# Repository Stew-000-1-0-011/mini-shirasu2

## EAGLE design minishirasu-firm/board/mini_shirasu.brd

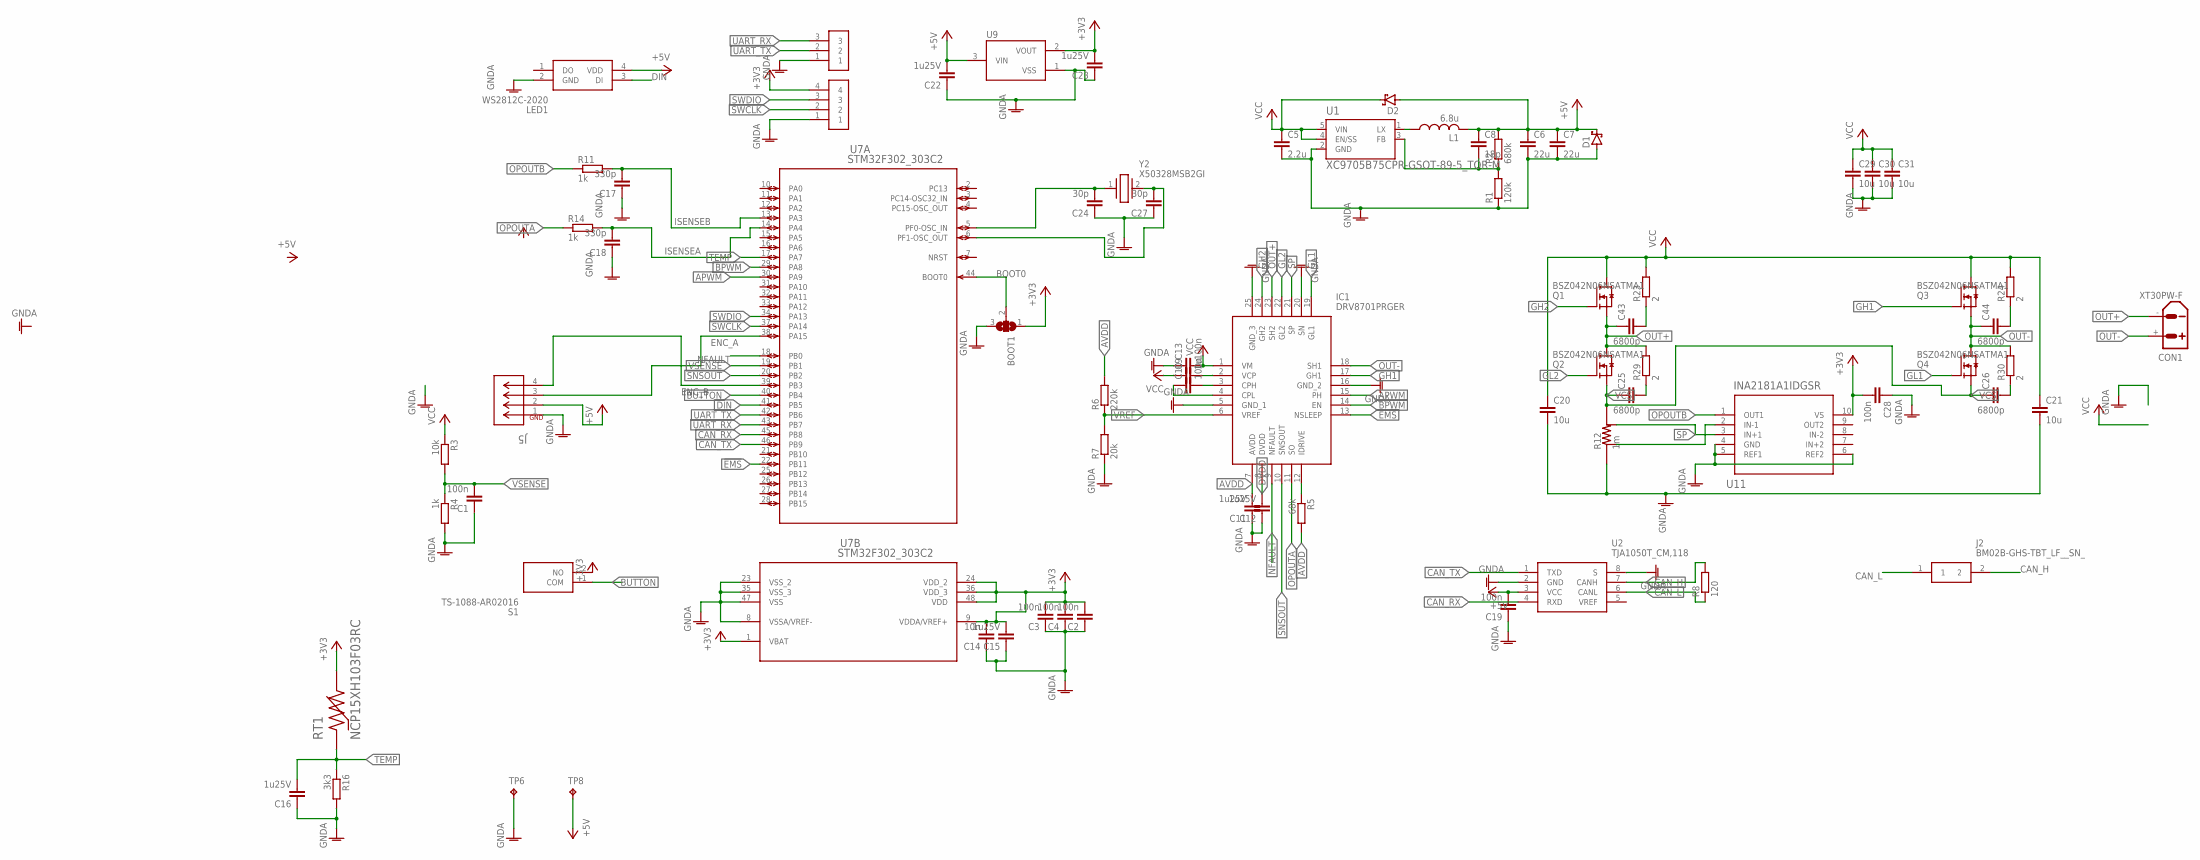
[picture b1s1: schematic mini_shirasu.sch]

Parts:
BOOT1: SJ2W; SJ_2
C1, C2, C3, C4, C10, C13, C19, C28: 100n; C0402
C5: 2.2u; C0805
C6, C7: 22u; C0805
C8: 18p; C0402
C9: 1u; C0603
C11, C12, C15, C16, C22, C23: 1u25V; C0402
C14: 10n; C0402
C17, C18: 330p; C0402
C20, C21, C29, C30, C31: 10u; C0805
C24, C27: 30p; C0402
C25, C26, C43, C44: 6800p; C0603
CON1: XT30PW-F
D1, D2: PMEG6010CEJ,115; SOD323_ST
IC1: DRV8701PRGER; QFN50P400X400X100-25N
J2: BM02B-GHS-TBT_LF__SN_; BM02B-GHS-TBT_1
J5: EP2.5-4-SIDE; CONN4_1744426-4
L1: 6.8u; INDUCTOR_1008
LED1: WS2812C-2020; WS2812C2020
Q1, Q2, Q3, Q4: BSZ042N06NSATMA1; TRANS_BSZ146N10LS5ATMA1
R1: 120k; R0402
R2: 680k; R0603
R3: 10k; R0402
R4, R11, R14: 1k; R0402
R5: 68k; R0402
R6: 220k; R0402
R7: 20k; R0402
R8: 120; R0603
R12: 1m; 2512-4PAD
R16: 3k3; R0402
R23, R24, R29, R30: 2; R0603
RT1: NCP15XH103F03RC; THRMC1005X55N
S1: TS-1088-AR02016; TS1088AR02016
TP6, TP8: TPB1,27; B1,27
U1: XC9705B75CPR-GSOT-89-5_TOR-M; SOT-89-5_TOR-M
U2: TJA1050T_CM,118; SOIC127P600X175-8N
U7: STM32F302_303C2; LQFP48-7X7MM
U9: XC6206; SOT95P240X110-3
U11: INA2181A1IDGSR; DGS10
U$1: PIN_HEADERPIN_HEADER; PIN_HEADER
U$2: 3PIN_HEADER
Y2: X50328MSB2GI; RESC5032X135N

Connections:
!EMS: IC1.13 (NSLEEP), U7.22 (PB11)
+3V3: BOOT1.1, C2.2, C3.2, C4.2, C14.2, C15.2, C23.2, C28.2, RT1.2, S1.2 (NO), U7.1 (VBAT), U7.9 (VDDA/VREF+), U7.24 (VDD_2), U7.36 (VDD_3), U7.48 (VDD), U9.2 (VOUT), U11.10 (VS), U$1.4
+5V: C6.1, C7.1, C8.1, C19.2, C22.2, D1.C, D2.A, J5.2, L1.P$2 (2), LED1.4 (VDD), R2.2, TP8.TP, U2.3 (VCC), U9.3 (VIN)
APWM: IC1.15 (PH), U7.30 (PA9)
AVDD: C11.2, IC1.7 (AVDD), R5.2, R6.2
BOOT0: BOOT1.2, U7.44 (BOOT0)
BPWM: IC1.14 (EN), U7.29 (PA8)
BUTTON: S1.1 (COM), U7.40 (PB4)
CAN_H: J2.2, R8.2, U2.7 (CANH)
CAN_L: J2.1, R8.1, U2.6 (CANL)
CAN_RX: U2.4 (RXD), U7.45 (PB8)
CAN_TX: U2.1 (TXD), U7.46 (PB9)
CPH: C10.2, IC1.3 (CPH)
CPL: C10.1, IC1.4 (CPL)
DIN: LED1.3 (DI), U7.41 (PB5)
DVDD: C12.2, IC1.8 (DVDD)
ENC_A: J5.3, U7.38 (PA15)
ENC_B: J5.4, U7.39 (PB3)
FB: C8.2, R1.2, R2.1, U1.3 (FB)
GH1: IC1.17 (GH1), Q3.4 (G)
GH2: IC1.24 (GH2), Q1.4 (G)
GL1: IC1.19 (GL1), Q4.4 (G)
GL2: IC1.22 (GL2), Q2.4 (G)
GNDA: BOOT1.3, C1.1, C2.1, C3.1, C4.1, C5.2, C6.2, C7.2, C11.1, C12.1, C13.1, C14.1, C15.1, C16.1, C17.1, C18.1, C19.1, C20.2, C21.2, C22.1, C23.1, C24.1, C27.1, C28.1, C29.2, C30.2, C31.2, D1.A, IC1.5 (GND_1), IC1.16 (GND_2), IC1.20 (SN), IC1.25 (GND_3), J5.1, LED1.2 (GND), R1.1, R4.2, R7.1, R12.1, R12.2 (1), R16.2, TP6.TP, U1.2 (GND), U2.2 (GND), U2.8 (S), U7.8 (VSSA/VREF-), U7.23 (VSS_2), U7.35 (VSS_3), U7.47 (VSS), U9.1 (VSS), U11.4 (GND), U11.5 (REF1), U11.6 (REF2), U$1.1, U$2.1
IDRIVE: IC1.12 (IDRIVE), R5.1
ISENSEA: C18.2, R14.2, U7.14 (PA4)
ISENSEB: C17.2, R11.2, U7.13 (PA3)
LX: L1.P$1 (1), U1.1 (LX)
unnamed: C25.2, R29.1
unnamed: C26.2, R30.1
unnamed: C24.2, U7.5 (PF0-OSC_IN), Y2.1
unnamed: C27.2, U7.6 (PF1-OSC_OUT), Y2.2
unnamed: R12.5 (3), U11.2 (IN-1)
unnamed: C44.2, R24.1
unnamed: C43.2, R23.1
NFAULT: IC1.9 (NFAULT), U7.18 (PB0)
OPOUTA: IC1.11 (SO), R14.1
OPOUTB: R11.1, U11.1 (OUT1)
OUT+: C43.1, CON1.-, IC1.23 (SH2), Q1.1_3 (S), Q2.5_8 (D), R29.2
OUT-: C44.1, CON1.+, IC1.18 (SH1), Q3.1_3 (S), Q4.5_8 (D), R30.2
SNSOUT: IC1.10 (SNSOUT), U7.20 (PB2)
SP: IC1.21 (SP), R12.6 (4), U11.3 (IN+1)
SWCLK: U7.37 (PA14), U$1.2
SWDIO: U7.34 (PA13), U$1.3
TEMP: C16.2, R16.1, RT1.1, U7.17 (PA7)
UART_RX: U7.43 (PB7), U$2.3
UART_TX: U7.42 (PB6), U$2.2
VCC: C5.1, C9.1, C13.2, C20.1, C21.1, C29.1, C30.1, C31.1, D2.C, IC1.1 (VM), Q1.5_8 (D), Q3.5_8 (D), R3.1, R23.2, R24.2, U1.4 (EN/SS), U1.5 (VIN)
VCP: C9.2, IC1.2 (VCP)
VCS: C25.1, C26.1, Q2.1_3 (S), Q4.1_3 (S), R12.3 (2), R12.4 (2)
VREF: IC1.6 (VREF), R6.1, R7.2
VSENSE: C1.2, R3.2, R4.1, U7.19 (PB1)

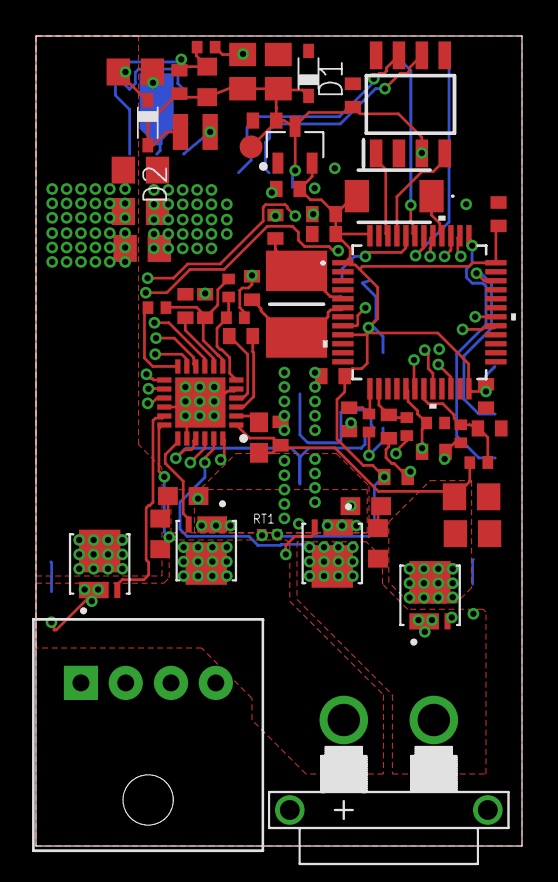
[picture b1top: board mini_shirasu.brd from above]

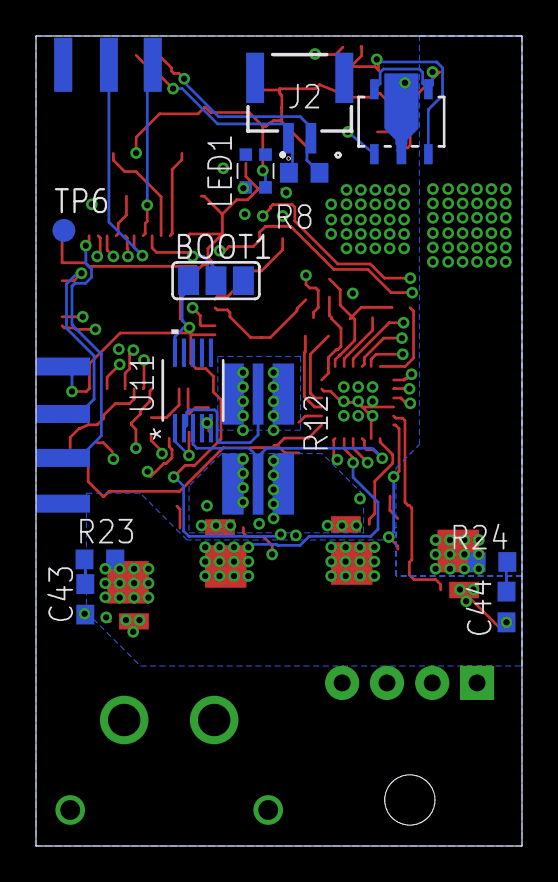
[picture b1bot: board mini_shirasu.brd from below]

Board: 4 copper layers, 27.0 x 45.0 mm, 74 parts (14 on the bottom side), 52 nets.

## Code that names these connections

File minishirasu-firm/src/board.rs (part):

//! レジスタ操作。2025-12-02版の基板(ドライバはDRV8701、水晶は8MHz)のピン配置:
//! - PA8: EN(TIM1 CH1、PWM)、PA9: PH(TIM1 CH2、向き)
//! - PB11: NSLEEP(!EMS)、PB0: NFAULT、PB2: SNSOUT(使っていない)
//! - PA3: ISENSEB(INA2181、ADC ch3)、PA4: ISENSEA(DRV8701のSO、使っていない)
//! - PB1: VSENSE(ADC ch9)、PA7: TEMP(ADC ch7)
//! - PA15/PB3: エンコーダ(TIM2の部分リマップ)
//! - PB8/PB9: CAN

use minishirasu_firm::config::PWM_ARR;
use minishirasu_firm::pwm::Compare;
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/// サンプル窓の中央を谷(ONパルスの中央)に合わせる
const ADC_TRIGGER_CCR: u16 = 23;

const CH_ISENSEB: u8 = 3; // PA3
const CH_TEMP: u8 = 7; // PA7
const CH_VSENSE: u8 = 9; // PB1

/// DRV8701がNSLEEPを上げてから動けるようになるまでの待ち[ms]。
/// データシートのtWAKEより長くとる。実機で足りなければ延ばす
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    while !p.RCC.cfgr.read().sws().is_pll() {}
}

/// PA8/PA9: TIM1 AF push-pull。PA3(ISENSEB), PA4(ISENSEA), PA7(TEMP), PB1(VSENSE): アナログ入力
/// PB11(NSLEEP): 出力(Low), PB0(NFAULT): 入力プルアップ
/// PA15/PB3(エンコーダ): 入力フローティング(リセット値のまま)
/// PB8(CAN RX): 入力プルアップ, PB9(CAN TX): AF push-pull
fn gpio_init(p: &pac::Peripherals) {
    p.RCC.apb2enr.modify(|_, w| {
        w.iopaen().set_bit().iopben().set_bit().tim1en().set_bit().afioen().set_bit().adc1en().set_bit()
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    // idleのwfi中にデバッガからメモリを読めず、RTTのログが届かない
    p.RCC.ahbenr.modify(|_, w| w.dma1en().set_bit());

    // GPIOA CRL: PA3, PA4, PA7 = 0b0000(アナログ入力)。
    // PA4はDRV8701のSOが1k越しにつながっているので、出力にしない
    p.GPIOA.crl.modify(|r, w| unsafe { w.bits(r.bits() & !((0xF << 12) | (0xF << 16) | (0xF << 28))) });
    // GPIOA CRH: PA8, PA9 = 0b1011(AF出力PP 50MHz)
    p.GPIOA.crh.modify(|r, w| unsafe {
        let mut v = r.bits();
        v &= !((0xF << 0) | (0xF << 4));
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
    // NSLEEPは先にLow(スリープ)、NFAULTとCAN RXはプルアップ
    p.GPIOB.bsrr.write(|w| w.br11().set_bit().bs0().set_bit().bs8().set_bit());
    // GPIOB CRL: PB0 = 0b1000(入力プル), PB1 = 0b0000(アナログ入力)
    p.GPIOB.crl.modify(|r, w| unsafe {
        let mut v = r.bits();
        v &= !((0xF << 0) | (0xF << 4));
        v |= 0b1000 << 0;
        w.bits(v)
    });
    // GPIOB CRH: PB8 = 0b1000(入力プル), PB9 = 0b1011(AF出力PP 50MHz), PB11 = 0b0010(出力PP 2MHz)
    p.GPIOB.crh.modify(|r, w| unsafe {
        let mut v = r.bits();
        v &= !((0xF << 0) | (0xF << 4) | (0xF << 12));
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        w.bits(v)
    });

    // CANをPB8/PB9へ(CAN_REMAP = 10)。TIM2のCH1/CH2をPA15/PB3へ(TIM2_REMAP = 01)。
    // PA15とPB3はJTAGのピンなので、SWJ_CFG = 010でJTAGを切ってSWDだけ残す。
    // SWJ_CFGは書き込み専用で読み値が不定なので、modifyでも毎回書く。
    // 書かないと読んだゴミが書き戻され、デバッガがつながらなくなることがある
    p.AFIO
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
/// コンペア値を書く。プリロードなので、次の更新イベント(山)で反映される
pub fn set_compare(c: Compare) {
    // PA8(EN)=CH1, PA9(PH)=CH2
    tim1().ccr1().write(|w| w.ccr().bits(c.en));
    tim1().ccr2().write(|w| w.ccr().bits(c.ph));
}
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    gpiob().bsrr.write(|w| w.br11().set_bit());
}

/// NFAULT(PB0)はLowで異常
pub fn nfault_asserted() -> bool {
    gpiob().idr.read().idr0().bit_is_clear()
}
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

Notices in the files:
parts and their libraries:
COPYRIGHT: Copyright (C) 2018 Accelerated Designs. All rights reserved
COPYRIGHT: Copyright (C) 2016 Accelerated Designs. All rights reserved
